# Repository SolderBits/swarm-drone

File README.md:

# swarm-drone
A small swarm of cheap quadcopters that fly inside a motion-capture rig built from USB cameras. It's based on Joshua Bird's Low-Cost-Mocap, and I've changed a lot of it with max imagination esp-fly drone.

It all started when I watched a video on a drone light show. I was honestly amazed by how so many drones could fly together and make those cool patterns. I don't know much about drones at all, so naturally I researched a little. I started looking into how to make a few drones and make a lighting show like that, but found out it's not as simple as it looks and took up this challenge.

First I started with the normal generic drone people build in videos with generic motors, but after a quick BOM I found out it costs way too much. After some searching I found this ESP mini drone which I wanted to build, but I didn't know how to do the lighting show, so I went online looking for cheaper alternatives and found a cool repo by Joshua Bird (Low-Cost-Mocap) where he uses PS3 cameras to get the position of an ESP drone. That is cheap and could achieve my aim, so I started building this project.

## How it works

Two cameras watch three infrared LEDs on each drone. The Python backend in Mocap/computer_code/api/ finds the LED spots, works out where each drone is and which way it faces, and smooths the result with a Kalman filter. A ground ESP32 runs the position and velocity PIDs and sends stick commands to each drone over ESP-NOW. Each drone runs ESP-FC, so the flight controller handles the motors.

## 3D Model

## Schematics

## PCB

### Assembled

## BOM

| Item | Quantity | Price (INR) | Price (USD) | Link |
|---|---|---|---|---|
| Seeed XIAO ESP32-S3 | 2 | ₹2278.00 | $23.98 | [Link](https://robu.in/product/seeed-studio-xiao-esp32s3-2-4ghz-wifi-ble-5-0/) |
| GY-521 MPU-6050 IMU | 2 | ₹254.00 | $2.68 | [Link](https://quartzcomponents.com/products/mpu6050-gyroscope-accelerometer-sensor) |
| AO3400 MOSFET (SOT-23) | 15 | ₹90.00 | $0.96 | [Link](https://quartzcomponents.com/products/ao3400-mosfet-30v-5-8a-a09t-sot-23-c-n-channel-smd-package) |
| 1N5819 Schottky Diode | 15 | ₹45.00 | $0.48 | [Link](https://quartzcomponents.com/products/1n5819-shottky-barrier-diode) |
| 100Ω Resistor | 20 | ₹14.00 | $0.14 | [Link](https://quartzcomponents.com/products/100-ohm-1-4-watt-resistor) |
| 10kΩ Resistor | 20 | ₹14.00 | $0.14 | [Link](https://quartzcomponents.com/products/10k-ohm-1-4-watt-resistor) |
| 100kΩ Resistor | 10 | ₹6.00 | $0.06 | [Link](https://quartzcomponents.com/products/100k-ohm-1-4-watt-resistor) |
| 68Ω Resistor | 20 | ₹14.00 | $0.14 | [Link](https://quartzcomponents.com/products/68-ohm-1-4-watt-resistor-with-5-tolerance-pack-of-10) |
| 100µF Capacitor | 2 | ₹6.00 | $0.06 | [Link](https://quartzcomponents.com/products/100uf-25v-radial-electrolytic-capacitor) |
| 100nF Ceramic Capacitor | 25 | ₹19.00 | $0.20 | [Link](https://makerbazar.in/products/ceramic-capacitor) |
| MX2.0 Battery Connector (with wire) | 2 | ₹78.00 | $0.82 | [Link](https://makerbazar.in/products/mx-pair-connector-with-wire-2-0mm-battery-charging-cable) |
| Male Header Pins (40 pin strip) | 2 | ₹14.00 | $0.15 | [Link](https://quartzcomponents.com/products/40-pin-break-away-headers-straight-male-headers) |
| 720 Coreless Motors (2 CW + 2 CCW, with props) | 12 | ₹537.00 | $5.64 | [Link](https://makerbazar.in/products/magnetic-micro-coreless-motor-for-drones-quadcopters-rc-1) |
| 55mm Propellers | 4 | ₹39.00 | $0.41 | [Link](https://makerbazar.in/products/4pcs-55mm-mini-drone-propeller-set-cw-ccw-coreless-motor) |
| 1S LiPo 400mAh 30C | 3 | ₹711.00 | $7.47 | [Link](https://quartzcomponents.com/products/3-7v-30c-400mah-lithium-polymer-lipo-battery-yy702030) |
| 3mm IR LED | 12 | ₹60.00 | $0.63 | [Link](https://quartzcomponents.com/products/3mm-ir-transmitter-led) |
| TP4056 Charger Module | 1 | ₹18.00 | $0.19 | [Link](https://quartzcomponents.com/products/tp4056-battery-charging-protection-module-type-c) |
| 3.3kΩ Resistor | 10 | ₹7.00 | $0.07 | [Link](https://quartzcomponents.com/products/3-3k-ohm-1-4-watt-resistor) |
| M2 x 6mm Screws | 8 | ₹16.00 | $0.16 | [Link](https://quartzcomponents.com/products/m2-x-6mm-pan-head-phillips-screw-pack-of-4) |
| Double-Sided Foam Tape | 1 | ₹23.00 | $0.24 | [Link](https://quartzcomponents.com/products/white-sponge-double-sided-acrylic-foam-adhesive-tapes) |
| LiPo Battery Strap | 2 | ₹116.00 | $1.22 | [Link](https://robu.in/product/20cm-lipo-battery-strap-belt-reusable-cable-tie-wrap/) |
| 30AWG Silicone Wire Red (1m) | 1 | ₹16.00 | $0.17 | [Link](https://quartzcomponents.com/products/30awg-silicone-wire-red-1-meter-high-quality-ultra-flexible-wires) |
| 30AWG Silicone Wire Black (1m) | 1 | ₹16.00 | $0.17 | [Link](https://quartzcomponents.com/products/30awg-silicone-wire-black-1-meter-high-quality-ultra-flexible-wire) |
| Sony PlayStation 3 Eye Camera (used) | 2 | ₹1710.00 | $18.00 | [Link](https://www.ebay.com/itm/166793845723) |
| 850nm IR Bandpass Filter (replaces camera IR-cut filter) | 2 | ₹1710.00 | $18.00 | [Link](https://commonlands.com/products/850nm-bandpass-filter) |
| 12V 5A 60W Power Supply with 5.5mm DC Plug | 1 | ₹425.00 | $4.47 | [Link](https://robocraze.com/products/kento-g-12v-power-adapter-5a-60w-with-5-5mm-dc-plug-standard-ac-to-dc-power-supply) |
| Official Raspberry Pi USB 3.0 Hub | 1 | ₹1191.00 | $12.54 | [Link](https://robocraze.com/products/official-raspberry-pi-usb-3-hub) |
| Shipping | 1 | ₹1367.00 | $14.38 | |
| PCB Manufacturing | 5 | ₹1000.00 | $10.53 | [Link](https://robu.in/product/online-pcb-manufacturing-service/) |
| **TOTAL** | | **₹19115.50** | **$215.15** | |

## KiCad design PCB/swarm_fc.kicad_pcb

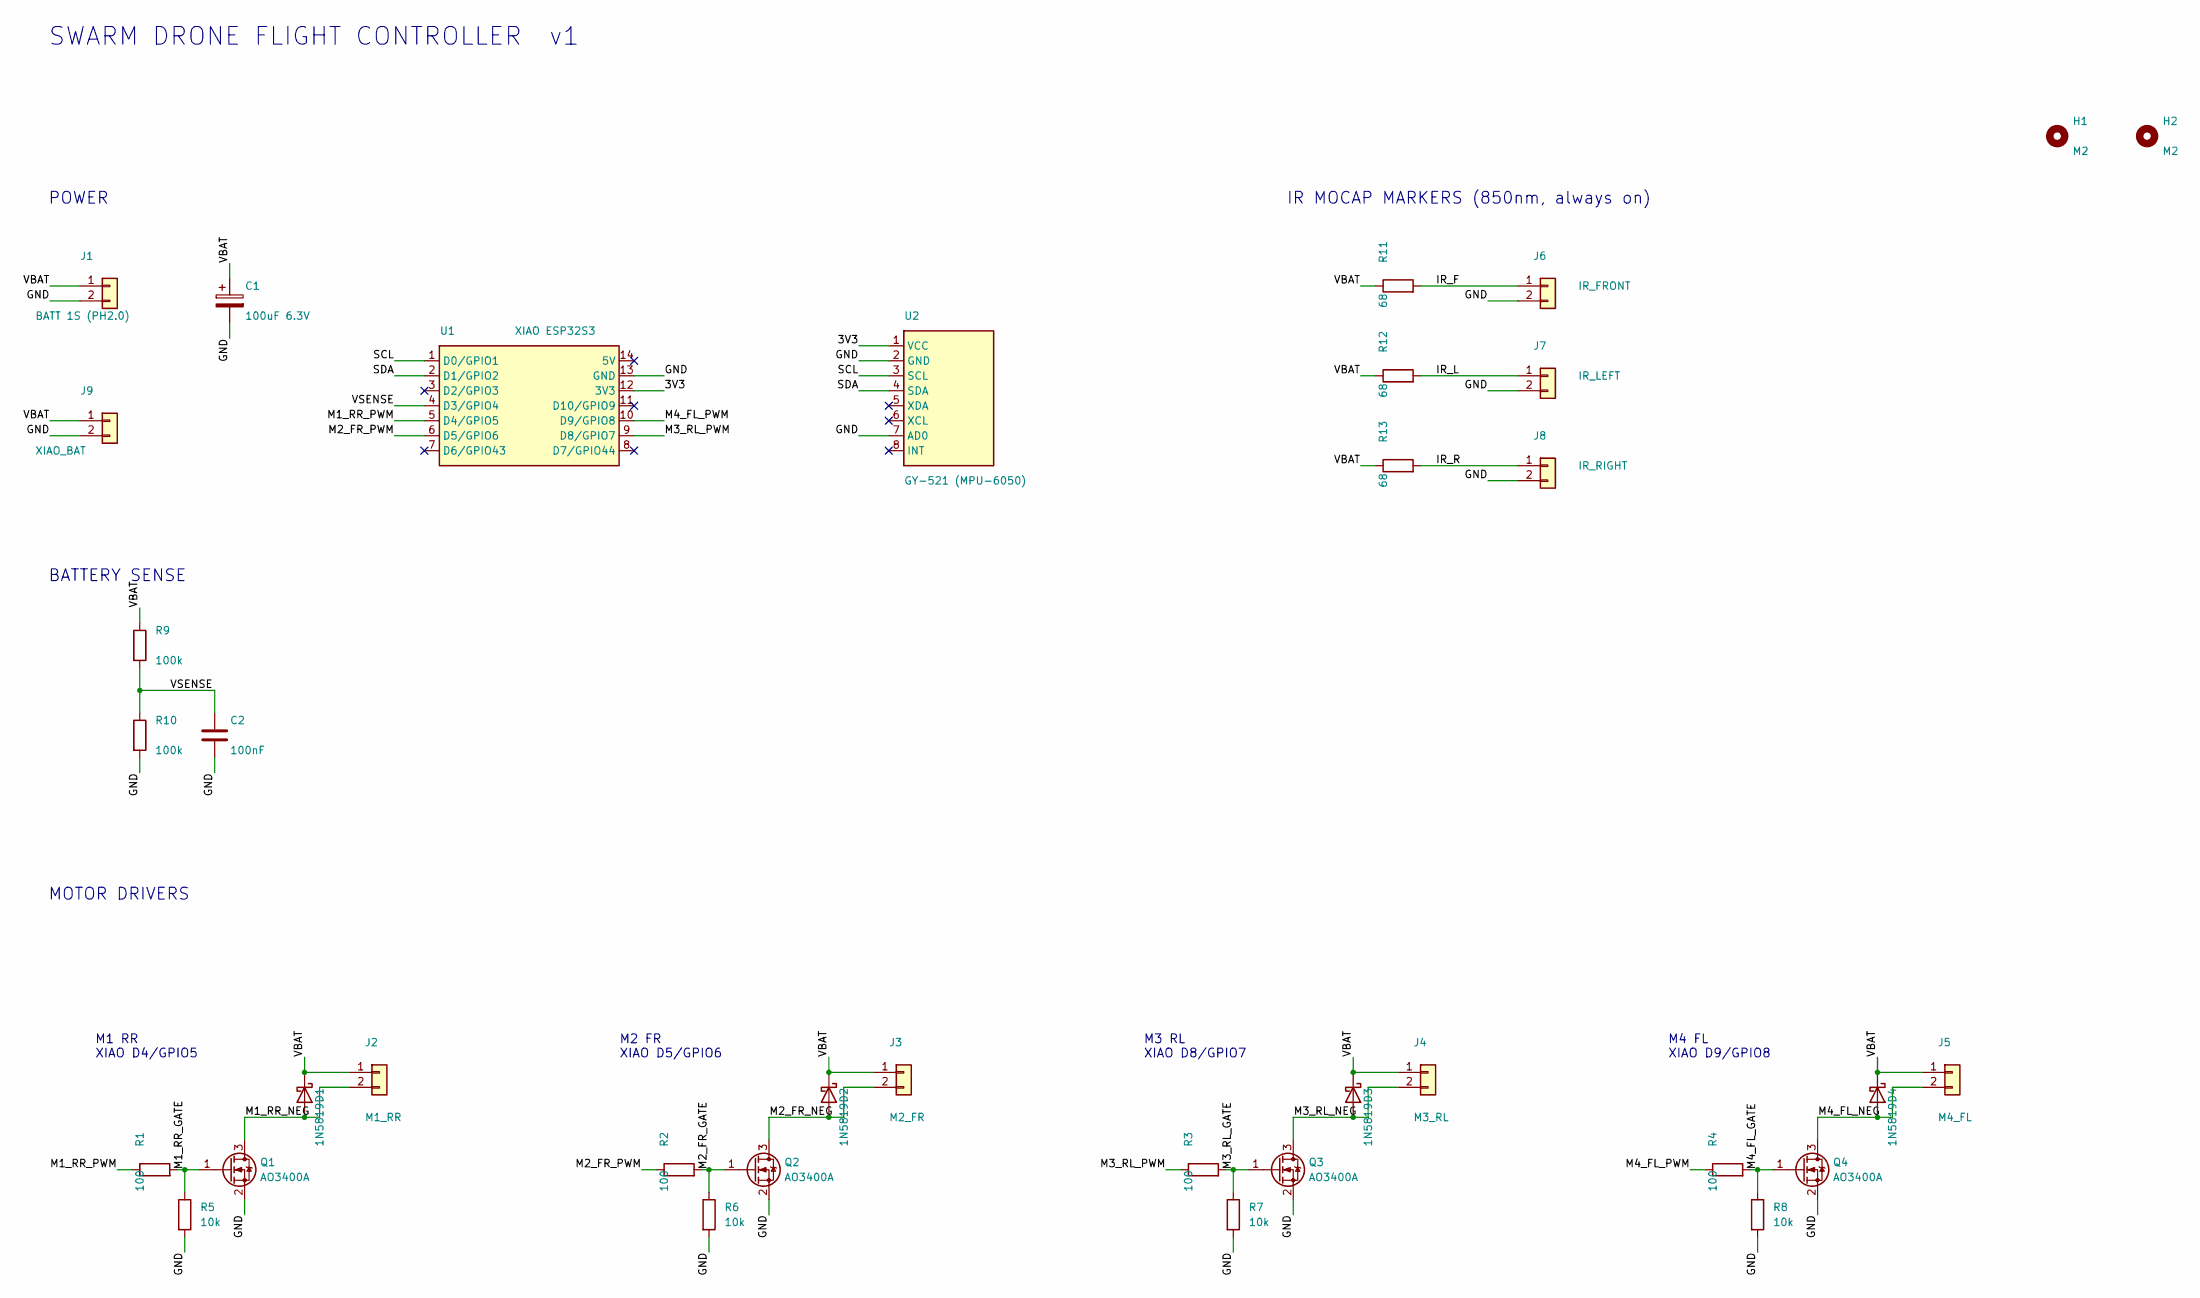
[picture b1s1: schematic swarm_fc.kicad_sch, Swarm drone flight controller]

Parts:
C1: 100uF 6.3V; CP_Radial_D5.0mm_P2.00mm
C2: 100nF; C_Disc_D3.0mm_W1.6mm_P2.50mm
D1, D2, D3, D4: 1N5819; D_DO-41_SOD81_P3.81mm_Vertical_KathodeUp
H1, H2: M2; MountingHole_2.2mm_M2
J1: BATT 1S (PH2.0); JST_PH_B2B-PH-K_1x02_P2.00mm_Vertical
J2: M1_RR; SolderWire-0.127sqmm_1x02_P3.7mm_D0.48mm_OD1mm
J3: M2_FR; SolderWire-0.127sqmm_1x02_P3.7mm_D0.48mm_OD1mm
J4: M3_RL; SolderWire-0.127sqmm_1x02_P3.7mm_D0.48mm_OD1mm
J5: M4_FL; SolderWire-0.127sqmm_1x02_P3.7mm_D0.48mm_OD1mm
J6: IR_FRONT; SolderWire-0.127sqmm_1x02_P3.7mm_D0.48mm_OD1mm
J7: IR_LEFT; SolderWire-0.127sqmm_1x02_P3.7mm_D0.48mm_OD1mm
J8: IR_RIGHT; SolderWire-0.127sqmm_1x02_P3.7mm_D0.48mm_OD1mm
J9: XIAO_BAT; SolderWire-0.127sqmm_1x02_P3.7mm_D0.48mm_OD1mm
Q1, Q2, Q3, Q4: AO3400A; SOT-23
R1, R2, R3, R4: 100; R_Axial_DIN0204_L3.6mm_D1.6mm_P2.54mm_Vertical
R5, R6, R7, R8: 10k; R_Axial_DIN0204_L3.6mm_D1.6mm_P2.54mm_Vertical
R9, R10: 100k; R_Axial_DIN0204_L3.6mm_D1.6mm_P2.54mm_Vertical
R11, R12, R13: 68; R_Axial_DIN0204_L3.6mm_D1.6mm_P2.54mm_Vertical
U1: XIAO ESP32S3; XIAO_ESP32S3_THT
U2: GY-521 (MPU-6050); GY-521_THT

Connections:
3V3: U1.12 (3V3), U2.1 (VCC)
GND: C1.2, C2.2, J1.2, J6.2, J7.2, J8.2, J9.2, Q1.2 (S), Q2.2 (S), Q3.2 (S), Q4.2 (S), R5.2, R6.2, R7.2, R8.2, R10.2, U1.13 (GND), U2.2 (GND), U2.7 (AD0)
IR_F: J6.1, R11.2
IR_L: J7.1, R12.2
IR_R: J8.1, R13.2
M1_RR_GATE: Q1.1 (G), R1.2, R5.1
M1_RR_NEG: D1.2 (A), J2.2, Q1.3 (D)
M1_RR_PWM: R1.1, U1.5 (D4/GPIO5)
M2_FR_GATE: Q2.1 (G), R2.2, R6.1
M2_FR_NEG: D2.2 (A), J3.2, Q2.3 (D)
M2_FR_PWM: R2.1, U1.6 (D5/GPIO6)
M3_RL_GATE: Q3.1 (G), R3.2, R7.1
M3_RL_NEG: D3.2 (A), J4.2, Q3.3 (D)
M3_RL_PWM: R3.1, U1.9 (D8/GPIO7)
M4_FL_GATE: Q4.1 (G), R4.2, R8.1
M4_FL_NEG: D4.2 (A), J5.2, Q4.3 (D)
M4_FL_PWM: R4.1, U1.10 (D9/GPIO8)
SCL: U1.1 (D0/GPIO1), U2.3 (SCL)
SDA: U1.2 (D1/GPIO2), U2.4 (SDA)
VBAT: C1.1, D1.1 (K), D2.1 (K), D3.1 (K), D4.1 (K), J1.1, J2.1, J3.1, J4.1, J5.1, J9.1, R9.1, R11.1, R12.1, R13.1
VSENSE: C2.1, R9.2, R10.1, U1.4 (D3/GPIO4)

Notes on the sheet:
IR MOCAP MARKERS (850nm, always on)
POWER
M2 FR XIAO D5/GPIO6
M1 RR XIAO D4/GPIO5
M3 RL XIAO D8/GPIO7
M4 FL XIAO D9/GPIO8
MOTOR DRIVERS
BATTERY SENSE
SWARM DRONE FLIGHT CONTROLLER v1

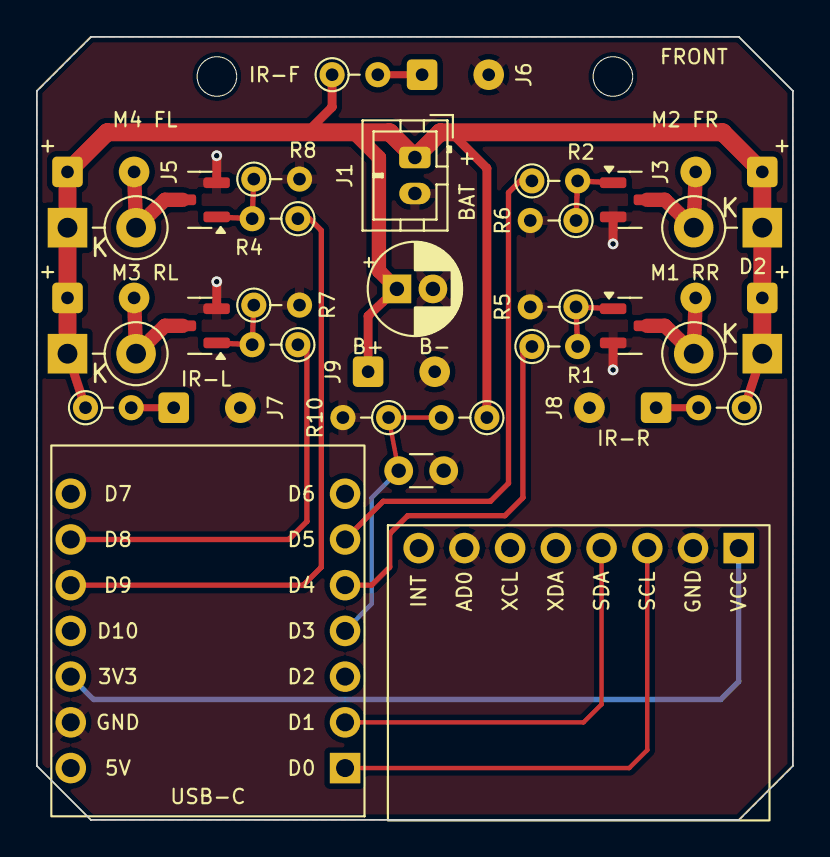
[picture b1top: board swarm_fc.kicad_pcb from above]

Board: 2 copper layers, 42.0 x 43.5 mm, 36 parts (0 on the bottom side), 21 nets.

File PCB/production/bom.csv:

Designator,Footprint,Quantity,Value,LCSC Part #
C1,CP_Radial_D5.0mm_P2.00mm,1,100uF 6.3V,
C2,C_Disc_D3.0mm_W1.6mm_P2.50mm,1,100nF,
"D1, D2, D3, D4",D_DO-41_SOD81_P3.81mm_Vertical_KathodeUp,4,1N5819,
J1,JST_PH_B2B-PH-K_1x02_P2.00mm_Vertical,1,BATT 1S (PH2.0),
"Q1, Q2, Q3, Q4",SOT-23,4,AO3400A,
"R1, R2, R3, R4",R_Axial_DIN0204_L3.6mm_D1.6mm_P2.54mm_Vertical,4,100,
"R10, R9",R_Axial_DIN0204_L3.6mm_D1.6mm_P2.54mm_Vertical,2,100k,
"R11, R12, R13",R_Axial_DIN0204_L3.6mm_D1.6mm_P2.54mm_Vertical,3,68,
"R5, R6, R7, R8",R_Axial_DIN0204_L3.6mm_D1.6mm_P2.54mm_Vertical,4,10k,
U1,XIAO_ESP32S3_THT,1,XIAO ESP32S3,
U2,GY-521_THT,1,GY-521 (MPU-6050),
